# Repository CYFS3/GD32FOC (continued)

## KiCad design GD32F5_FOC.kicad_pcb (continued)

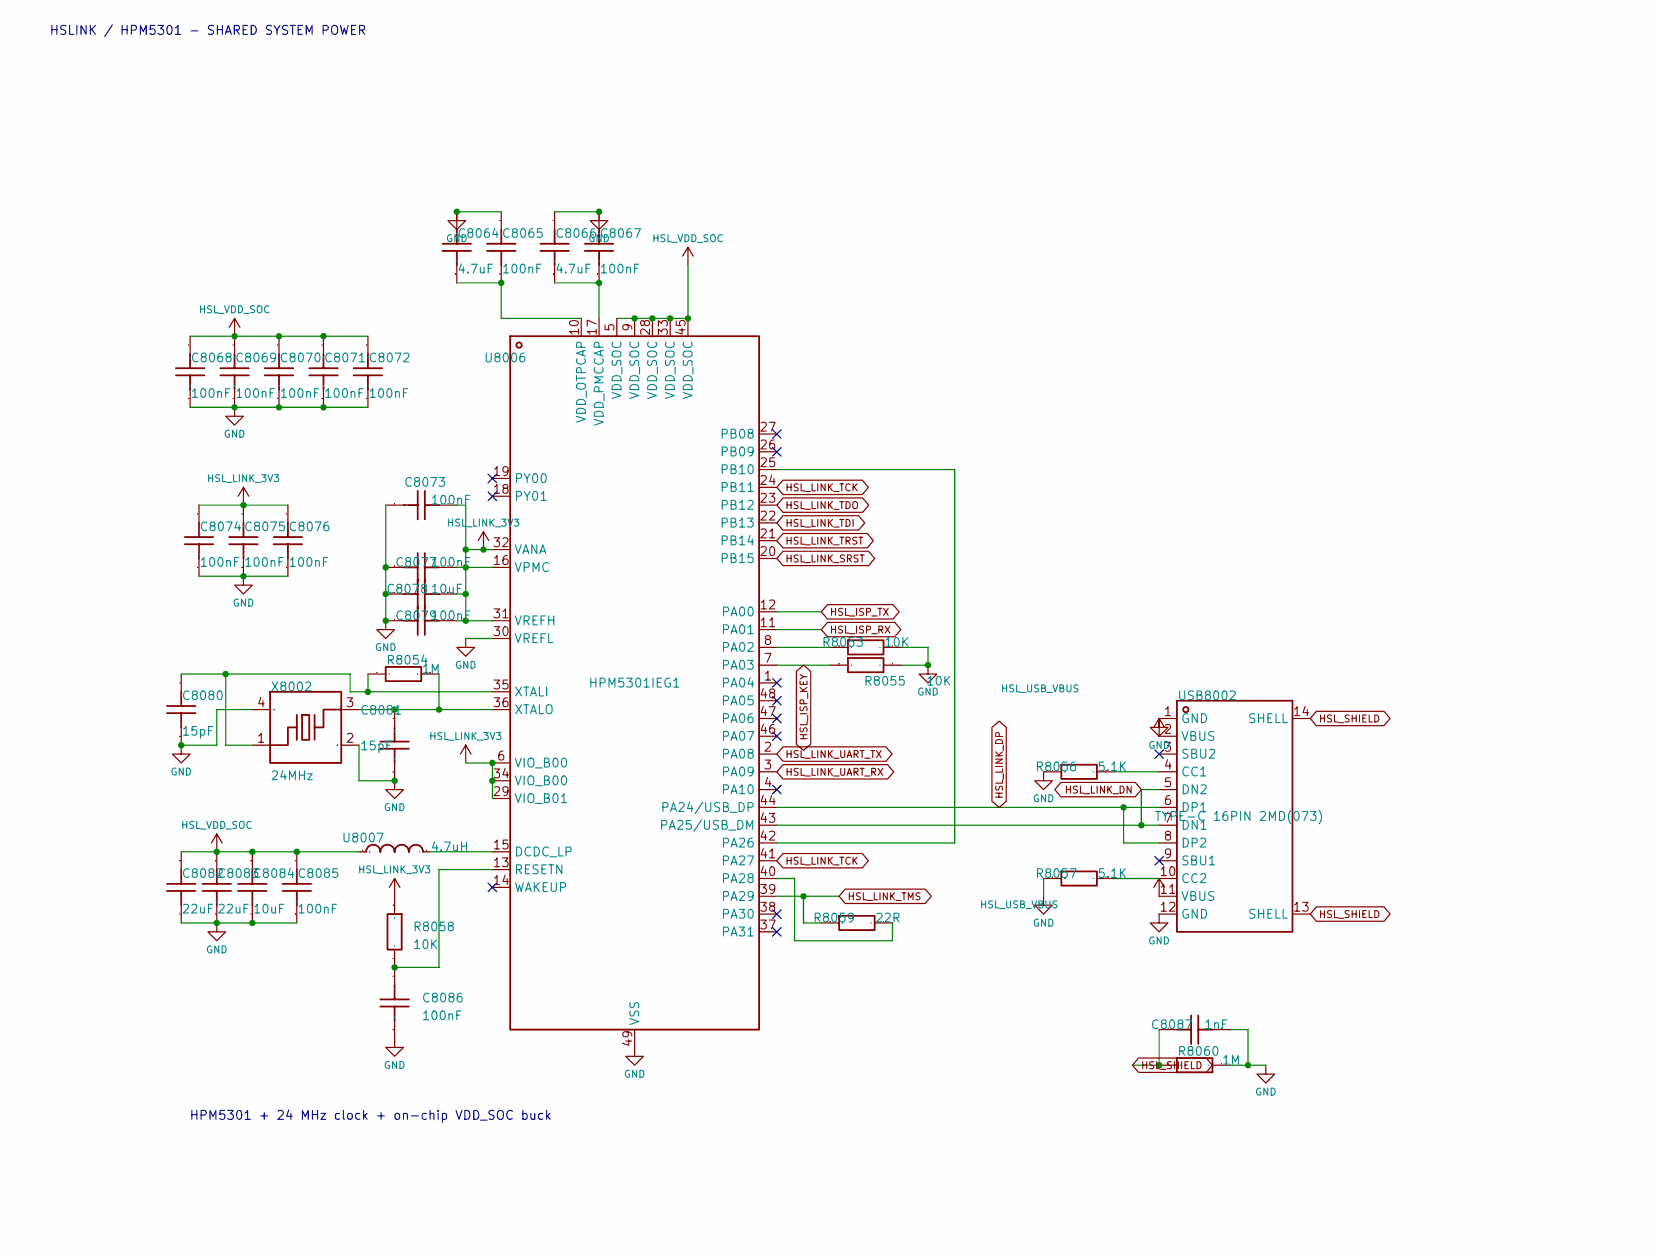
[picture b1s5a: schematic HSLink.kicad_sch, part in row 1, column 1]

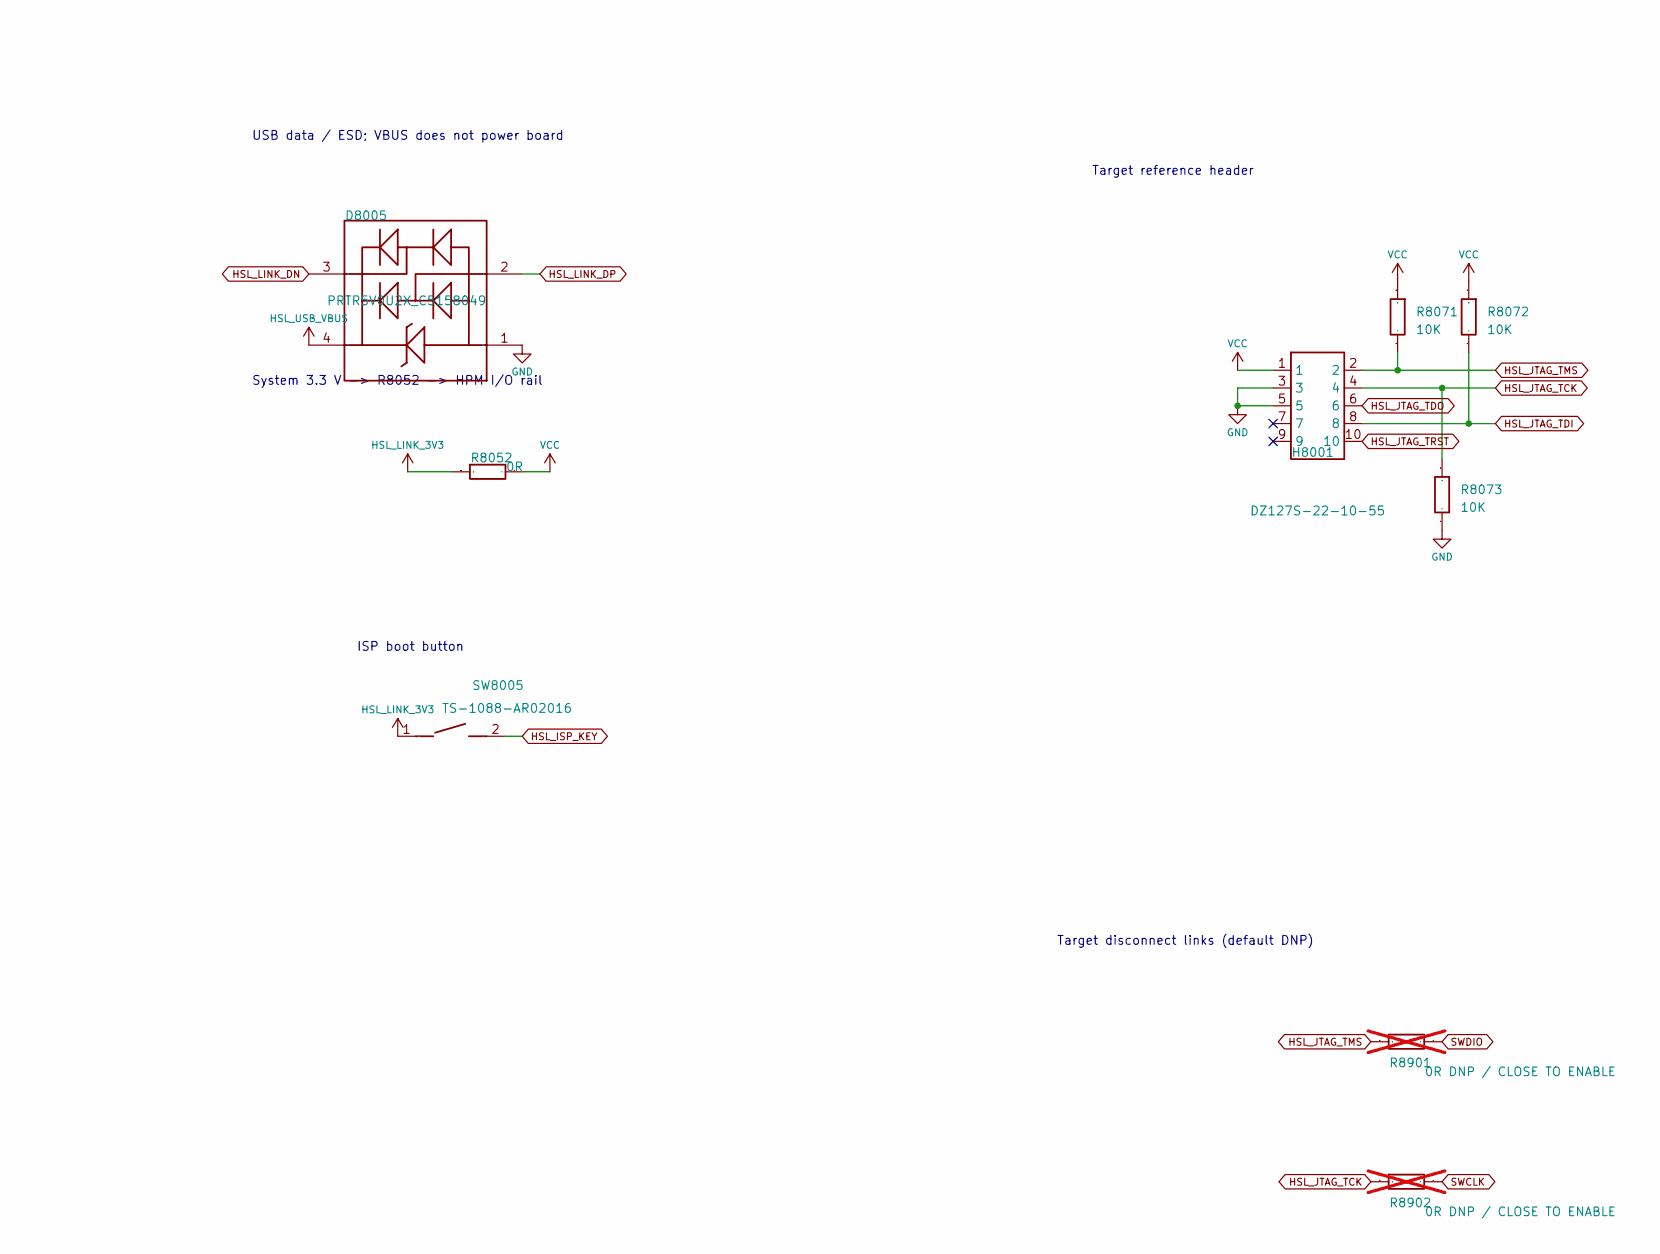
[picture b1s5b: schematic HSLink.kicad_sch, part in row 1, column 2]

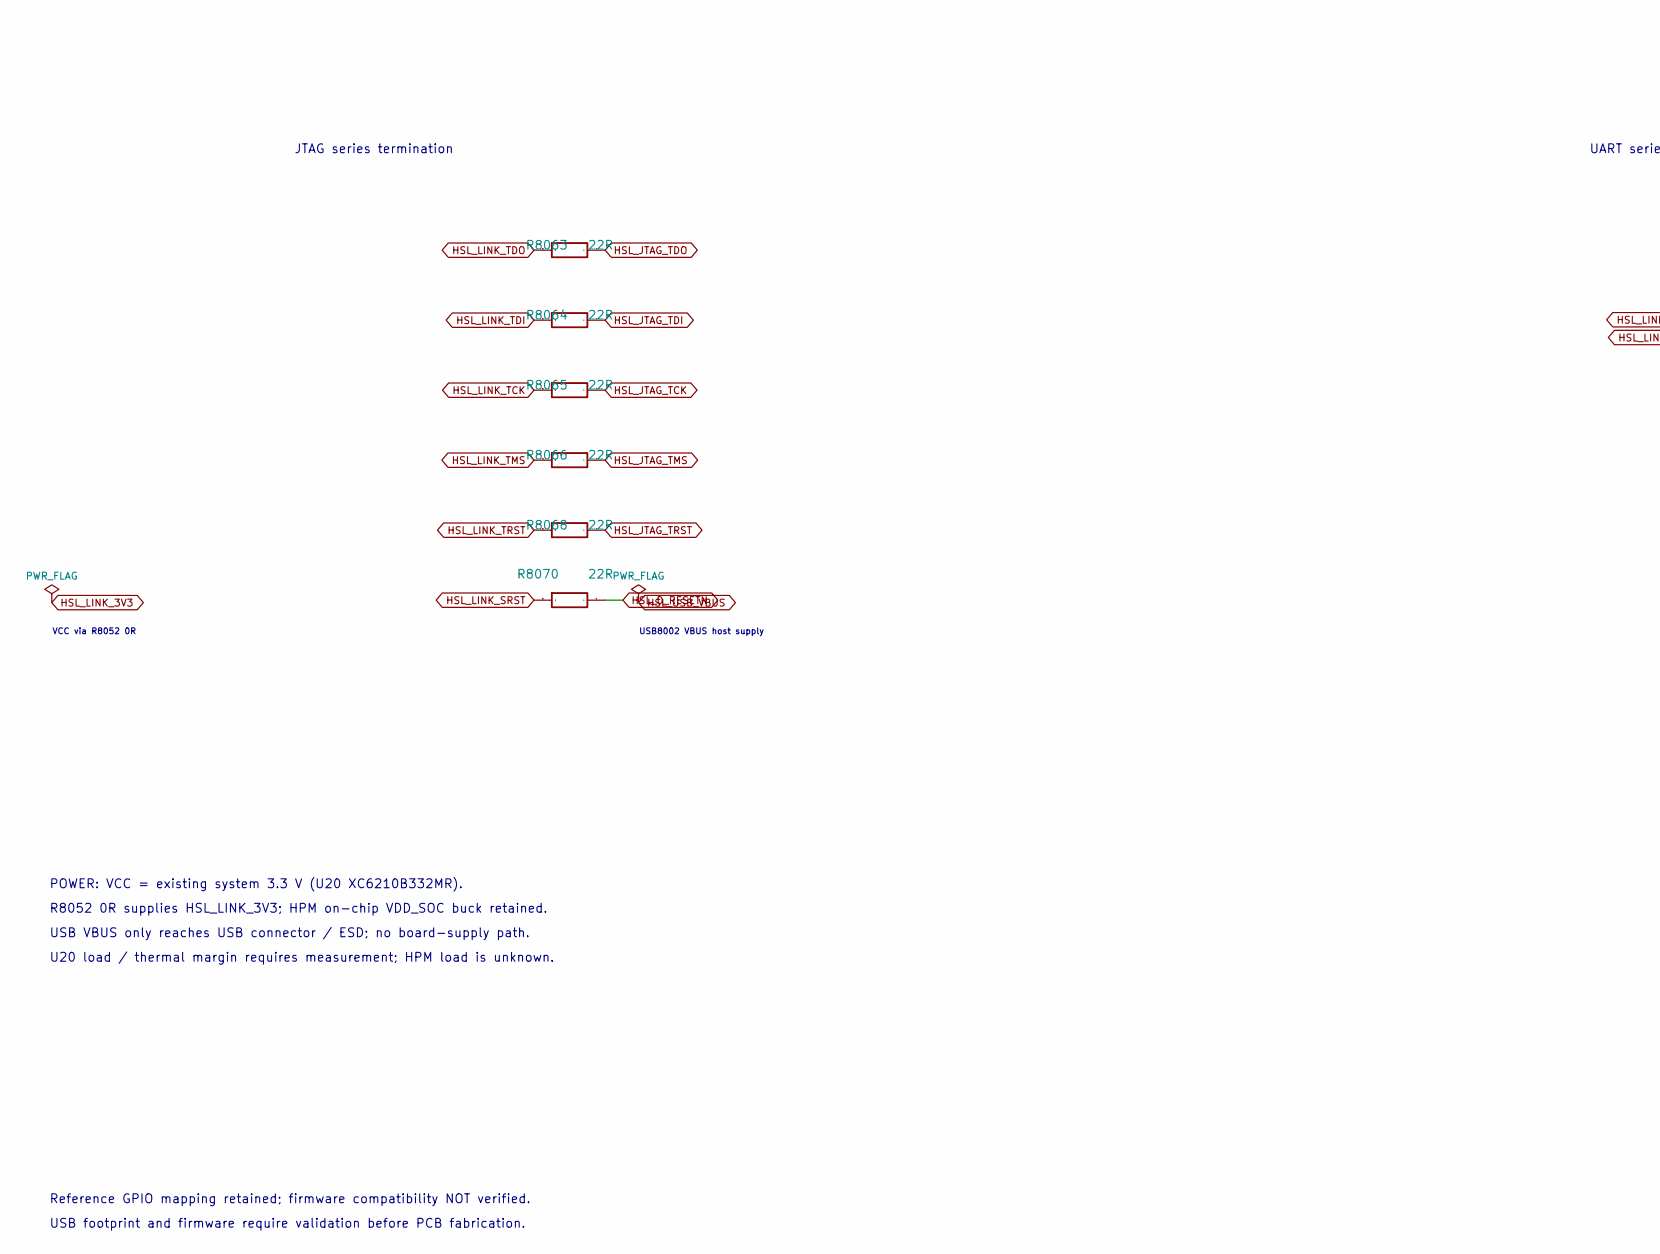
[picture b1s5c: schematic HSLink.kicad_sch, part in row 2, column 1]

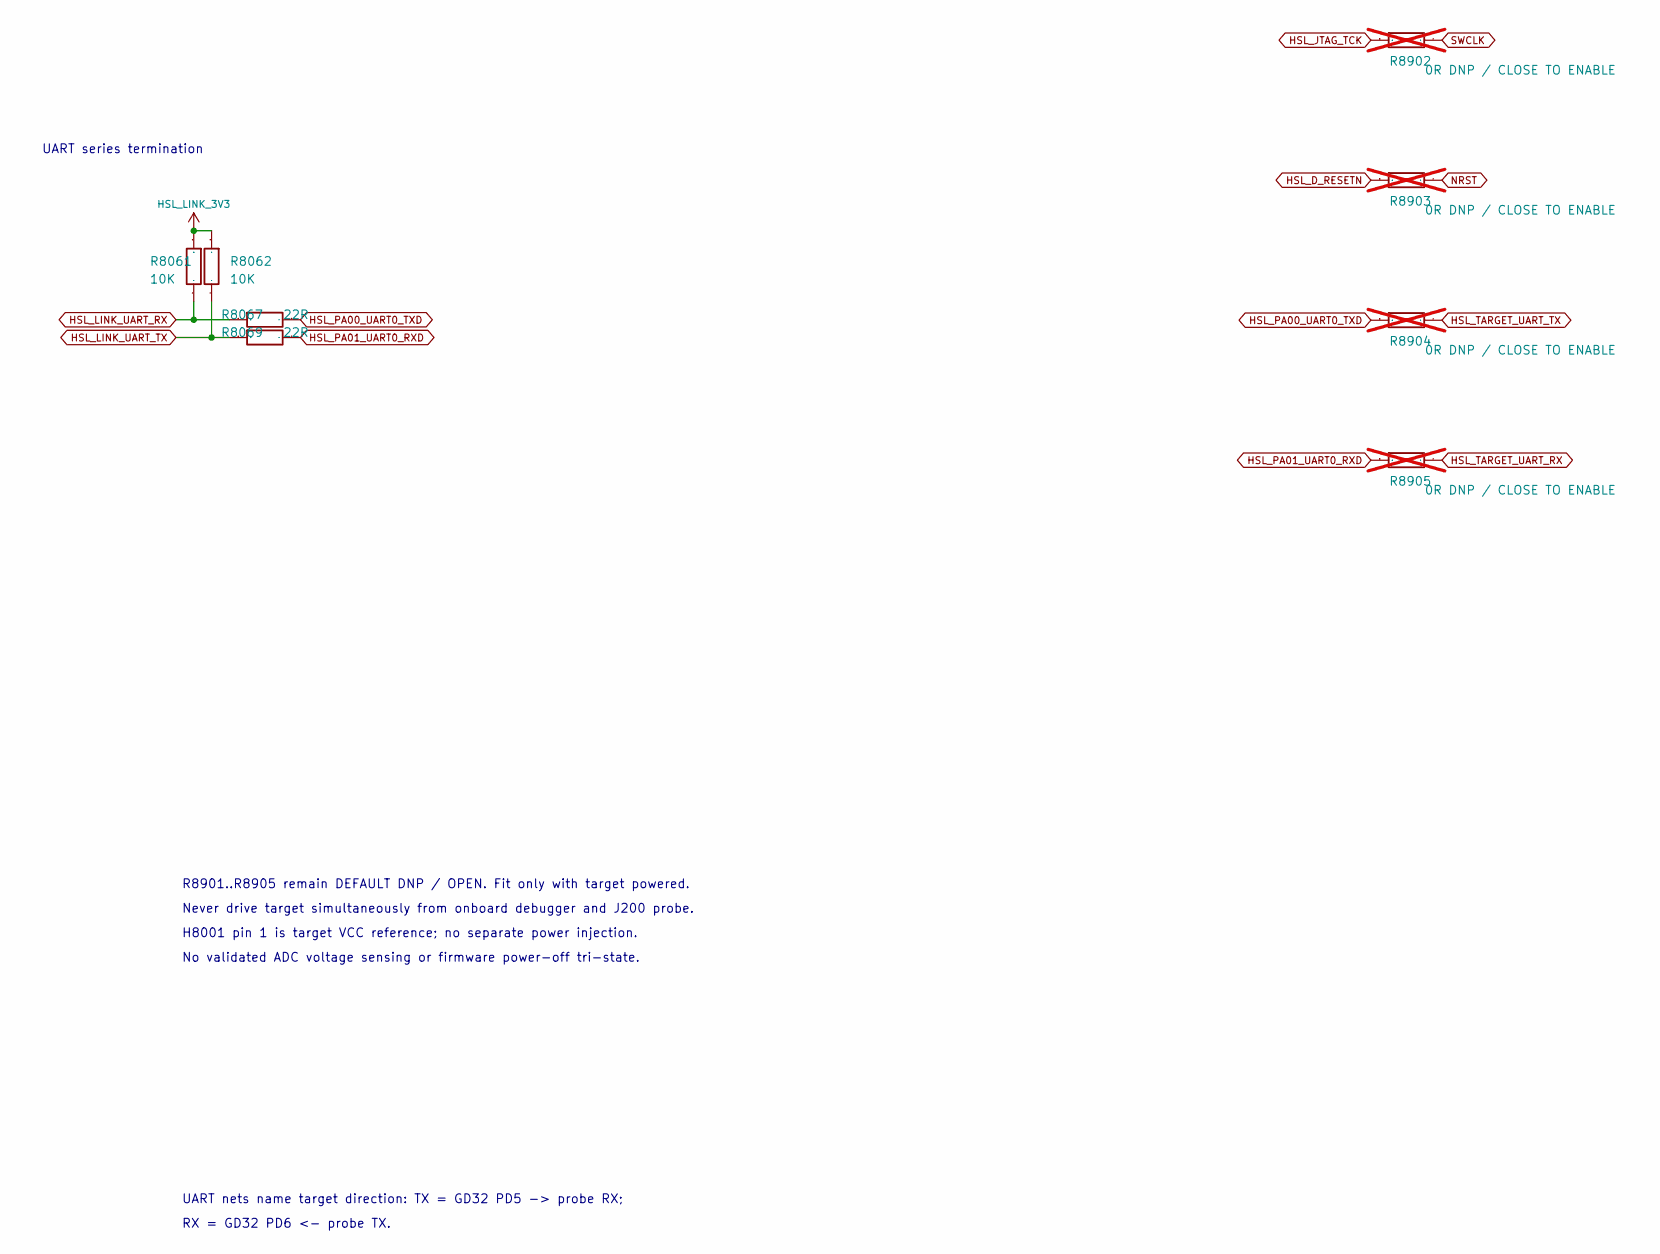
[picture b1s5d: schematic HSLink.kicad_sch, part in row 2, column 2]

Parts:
C8064, C8066: 4.7uF; C0603
C8065, C8067, C8068, C8069, C8070, C8071, C8072, C8073, C8074, C8075, C8076, C8077, C8079, C8085, C8086: 100nF; C0603
C8078, C8084: 10uF; C0603
C8080, C8081: 15pF; C0603
C8082, C8083: 22uF; C0603
C8087: 1nF; C0603
D8005: PRTR5V0U2X_C5158049; SOT-143_L2.9-W1.3-P1.92-LS2.3-BL; Manufacturer Part PRTR5V0U2X; LCSC Part Name ESD
H8001: DZ127S-22-10-55; HDR-SMD_10P-P1.27-V-M-R2-C5-S1.27-LS5.5; Manufacturer Part DZ127S-22-10-55; LCSC Part Name 2x5P 间距:1.27mm 方针 立贴
R8052: 0R; R0603
R8053, R8055, R8058, R8061, R8062, R8071, R8072, R8073: 10K; R0603
R8054, R8060: 1M; R0603
R8056, R8057: 5.1K; R0603
R8059, R8063, R8064, R8065, R8066, R8067, R8068, R8069, R8070: 22R; R0603
R8901, R8902, R8903, R8904, R8905: 0R DNP / CLOSE TO ENABLE; R0603; not fitted
SW8005: TS-1088-AR02016; SW-SMD_L3.9-W3.0-P4.45; Manufacturer Part TS-1088-AR02016; LCSC Part Name 4*3*2mm 立贴 轻触开关
U8006: HPM5301IEG1; QFN-48_L6.0-W6.0-P0.40-TL-EP4.2; Manufacturer Part HPM5301IEG1; LCSC Part Name HPM5301IEG1
U8007: 4.7uH; IND-SMD_L2.5-W2.0-VLS252012CX-150M; Manufacturer Part FTC252010S4R7MBCA; LCSC Part Name 4.7uH ±20% 2.6A
USB8002: TYPE-C 16PIN 2MD(073); USB-C-SMD_TYPE-C-6PIN-2MD-073; Manufacturer Part TYPE-C 16PIN 2MD(073); LCSC Part Name Type-C 母 卧贴
X8002: 24MHz; CRYSTAL-SMD_4P-L2.0-W1.6-BL-A; Manufacturer Part XL7EL89CKI-111YLC-24M; LCSC Part Name YSX211SL 24MHZ 4P 2016 8PF ±10PPM -40~8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

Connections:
GND: C8064.2, C8065.2, C8066.2, C8067.2, C8068.1, C8069.1, C8070.1, C8071.1, C8072.1, C8073.1, C8074.1, C8075.1, C8076.1, C8077.1, C8078.2, C8079.1, C8080.1, C8081.1, C8082.2, C8083.2, C8084.2, C8085.1, C8086.1, C8087.1, D8005.1, H8001.3, H8001.5, R8053.2, R8055.2, R8056.1, R8057.1, R8060.2, R8073.2, U8006.30 (VREFL), U8006.49 (VSS), USB8002.1 (GND), USB8002.12 (GND), X8002.2 (GND), X8002.4 (GND); also elsewhere on the board
HSL_D_RESETN: R8070.2, R8903.1
HSL_ISP_KEY: R8055.1, SW8005.2, U8006.7 (PA03)
HSL_ISP_RX: U8006.11 (PA01)
HSL_ISP_TX: U8006.12 (PA00)
HSL_JTAG_TCK: H8001.4, R8065.2, R8073.1, R8902.1
HSL_JTAG_TDI: H8001.8, R8064.2, R8072.2
HSL_JTAG_TDO: H8001.6, R8063.2
HSL_JTAG_TMS: H8001.2, R8066.2, R8071.2, R8901.1
HSL_JTAG_TRST: H8001.10, R8068.2
HSL_LINK_3V3: C8073.2, C8074.2, C8075.2, C8076.2, C8077.2, C8078.1, C8079.2, R8052.1, R8058.1, R8061.1, R8062.1, SW8005.1, U8006.6 (VIO_B00), U8006.16 (VPMC), U8006.29 (VIO_B01), U8006.31 (VREFH), U8006.32 (VANA), U8006.34 (VIO_B00)
HSL_LINK_DN: D8005.3, U8006.43 (PA25/USB_DM), USB8002.5 (DN2), USB8002.7 (DN1)
HSL_LINK_DP: D8005.2, U8006.44 (PA24/USB_DP), USB8002.6 (DP1), USB8002.8 (DP2)
HSL_LINK_SRST: R8070.1, U8006.20 (PB15)
HSL_LINK_TCK: R8065.1, U8006.24 (PB11), U8006.41 (PA27)
HSL_LINK_TDI: R8064.1, U8006.22 (PB13)
HSL_LINK_TDO: R8063.1, U8006.23 (PB12)
HSL_LINK_TMS: R8059.1, R8066.1, U8006.39 (PA29)
HSL_LINK_TRST: R8068.1, U8006.21 (PB14)
HSL_LINK_UART_RX: R8061.2, R8067.1, U8006.3 (PA09)
HSL_LINK_UART_TX: R8062.2, R8069.1, U8006.2 (PA08)
HSL_PA00_UART0_TXD: R8067.2, R8904.1
HSL_PA01_UART0_RXD: R8069.2, R8905.1
HSL_SHIELD: C8087.2, R8060.1, USB8002.13 (SHELL), USB8002.14 (SHELL)
HSL_TARGET_UART_RX: R8905.2; also elsewhere on the board
HSL_TARGET_UART_TX: R8904.2; also elsewhere on the board
HSL_USB_VBUS: D8005.4, USB8002.2 (VBUS), USB8002.11 (VBUS)
HSL_VDD_SOC: C8068.2, C8069.2, C8070.2, C8071.2, C8072.2, C8082.1, C8083.1, C8084.1, C8085.2, U8006.5 (VDD_SOC), U8006.9 (VDD_SOC), U8006.28 (VDD_SOC), U8006.33 (VDD_SOC), U8006.45 (VDD_SOC), U8007.1
NRST: R8903.2; also elsewhere on the board
unnamed: U8006.15 (DCDC_LP), U8007.2
unnamed: R8053.1, U8006.8 (PA02)
unnamed: U8006.25 (PB10), U8006.42 (PA26)
unnamed: R8059.2, U8006.40 (PA28)
unnamed: C8086.2, R8058.2, U8006.13 (RESETN)
unnamed: C8064.1, C8065.1, U8006.10 (VDD_OTPCAP)
unnamed: C8066.1, C8067.1, U8006.17 (VDD_PMCCAP)
unnamed: C8080.2, R8054.2, U8006.35 (XTALI), X8002.1
unnamed: C8081.2, R8054.1, U8006.36 (XTALO), X8002.3
unnamed: R8056.2, USB8002.4 (CC1)
unnamed: R8057.2, USB8002.10 (CC2)
SWCLK: R8902.2; also elsewhere on the board
SWDIO: R8901.2; also elsewhere on the board
VCC: H8001.1, R8052.2, R8071.1, R8072.1; also elsewhere on the board

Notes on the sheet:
Target disconnect links (default DNP)
U20 load / thermal margin requires measurement; HPM load is unknown.
ISP boot button
HSLINK / HPM5301 - SHARED SYSTEM POWER
USB data / ESD; VBUS does not power board
UART series termination
H8001 pin 1 is target VCC reference; no separate power injection.
No validated ADC voltage sensing or firmware power-off tri-state.
RX = GD32 PD6 <- probe TX.
USB VBUS only reaches USB connector / ESD; no board-supply path.
Target reference header
Never drive target simultaneously from onboard debugger and J200 probe.
Reference GPIO mapping retained; firmware compatibility NOT verified.
UART nets name target direction: TX = GD32 PD5 -> probe RX;
POWER: VCC = existing system 3.3 V (U20 XC6210B332MR).
System 3.3 V -> R8052 -> HPM I/O rail
HPM5301 + 24 MHz clock + on-chip VDD_SOC buck
R8052 0R supplies HSL_LINK_3V3; HPM on-chip VDD_SOC buck retained.
USB footprint and firmware require validation before PCB fabrication.
R8901..R8905 remain DEFAULT DNP / OPEN. Fit only with target powered.
JTAG series termination
VCC via R8052 0R
USB8002 VBUS host supply
